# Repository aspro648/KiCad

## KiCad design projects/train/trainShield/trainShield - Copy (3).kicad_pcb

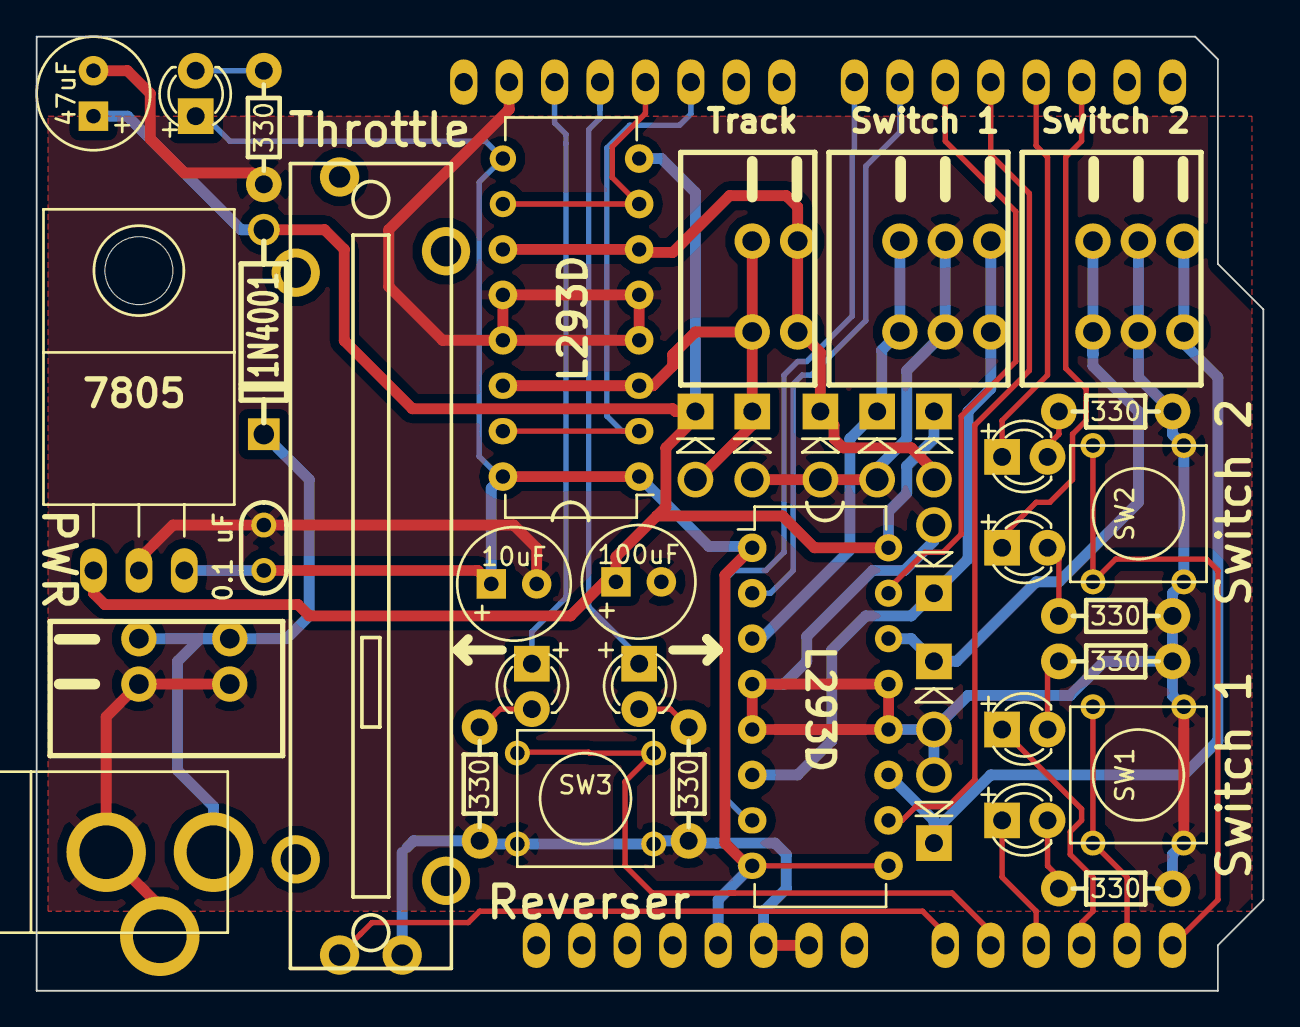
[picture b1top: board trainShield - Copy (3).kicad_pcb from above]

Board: 2 copper layers, 68.6 x 53.3 mm, 42 parts (0 on the bottom side), 33 nets.

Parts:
C1: 0.1 uF; C1
C2: 47uF; C2
C3: 100uF; C2
C4: 10uF; C2
C7: CTRIM; BOURNS-PTA3043_30mm-slide-pot
CON1: BARREL_JACK
D1: 1N4001
D2, D3, D4, D5, D6, D7, D8, D9: 1N4001; Diode_DO-41_SOD81_Vertical_AnodeUp
D10, D11, D12, D13, D14, D15, D16: LED; LED-3MM
P1, P3: TERM_2; TERMx2
P2, P4: TERMx3
R1, R2, R3, R4, R5, R6, R7: 330; Resistor_Horz
SHIELD1: ARDUINO_SHIELD
SW1, SW2, SW3: SW_PUSHBUTTON; SW_PUSH_SMALL
U1: 7805; TO-220_Neutral123_Horizontal
U2, U3: L293D; DIP-16_W7.62mm
VAL: MadeInOregonRev25
VAL#2: MB225rev

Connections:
+5V: C1.1, C4.1, D12.2, SHIELD1.5V, U1.VO, U2.1, U2.9, U2.16, U3.1, U3.8, U3.9
+12V: C2.1, C3.1, D1.1, D2.1, D7.1, U1.VI, U2.8, U3.16
/MOT_A: SHIELD1.11, U2.7, U2.10
/MOT_B: SHIELD1.10, U2.2, U2.15
/M_1: D3.1, D7.2, P1.1, U2.6, U2.11
/M_2: D2.2, D4.1, P1.2, U2.3, U2.14
/TURN_1_A: SHIELD1.5, U3.15
/TURN_1_B: SHIELD1.4, U3.10
/TURN_2_A: SHIELD1.6, U3.2
/TURN_2_B: SHIELD1.7, U3.7
GND: C1.2, C2.2, C3.2, C4.2, C7.2, CON1.2, CON1.3, D3.2, D4.2, D5.2, D6.2, D8.2, D9.2, P2.2, P3.2, P4.2, R1.1, R2.1, R3.1, R4.1, R5.1, R6.1, R7.1, SHIELD1.GND1, SHIELD1.GND2, SHIELD1.GND3, SW1.2, SW2.2, SW3.2, U1.GND, U2.4, U2.5, U2.12, U2.13, U3.4, U3.5, U3.12, U3.13
unnamed: C7.1, SHIELD1.AD0
unnamed: CON1.1, D1.2, P3.1
unnamed: D5.1, P2.3, U3.14
unnamed: D6.1, P2.1, U3.11
unnamed: D8.1, P4.3, U3.3
unnamed: D9.1, P4.1, U3.6
unnamed: D10.1, R5.2
unnamed: D10.2, SHIELD1.12
unnamed: D11.1, R6.2
unnamed: D11.2, SHIELD1.13
unnamed: D12.1, R1.2
unnamed: D13.1, R2.2
unnamed: D13.2, SHIELD1.3
unnamed: D14.1, R3.2
unnamed: D14.2, SHIELD1.2
unnamed: D15.1, R4.2
unnamed: D15.2, SHIELD1.AD3
unnamed: D16.1, R7.2
unnamed: D16.2, SHIELD1.AD2
unnamed: SHIELD1.AD1, SW3.1
unnamed: SHIELD1.AD4, SW1.1
unnamed: SHIELD1.AD5, SW2.1

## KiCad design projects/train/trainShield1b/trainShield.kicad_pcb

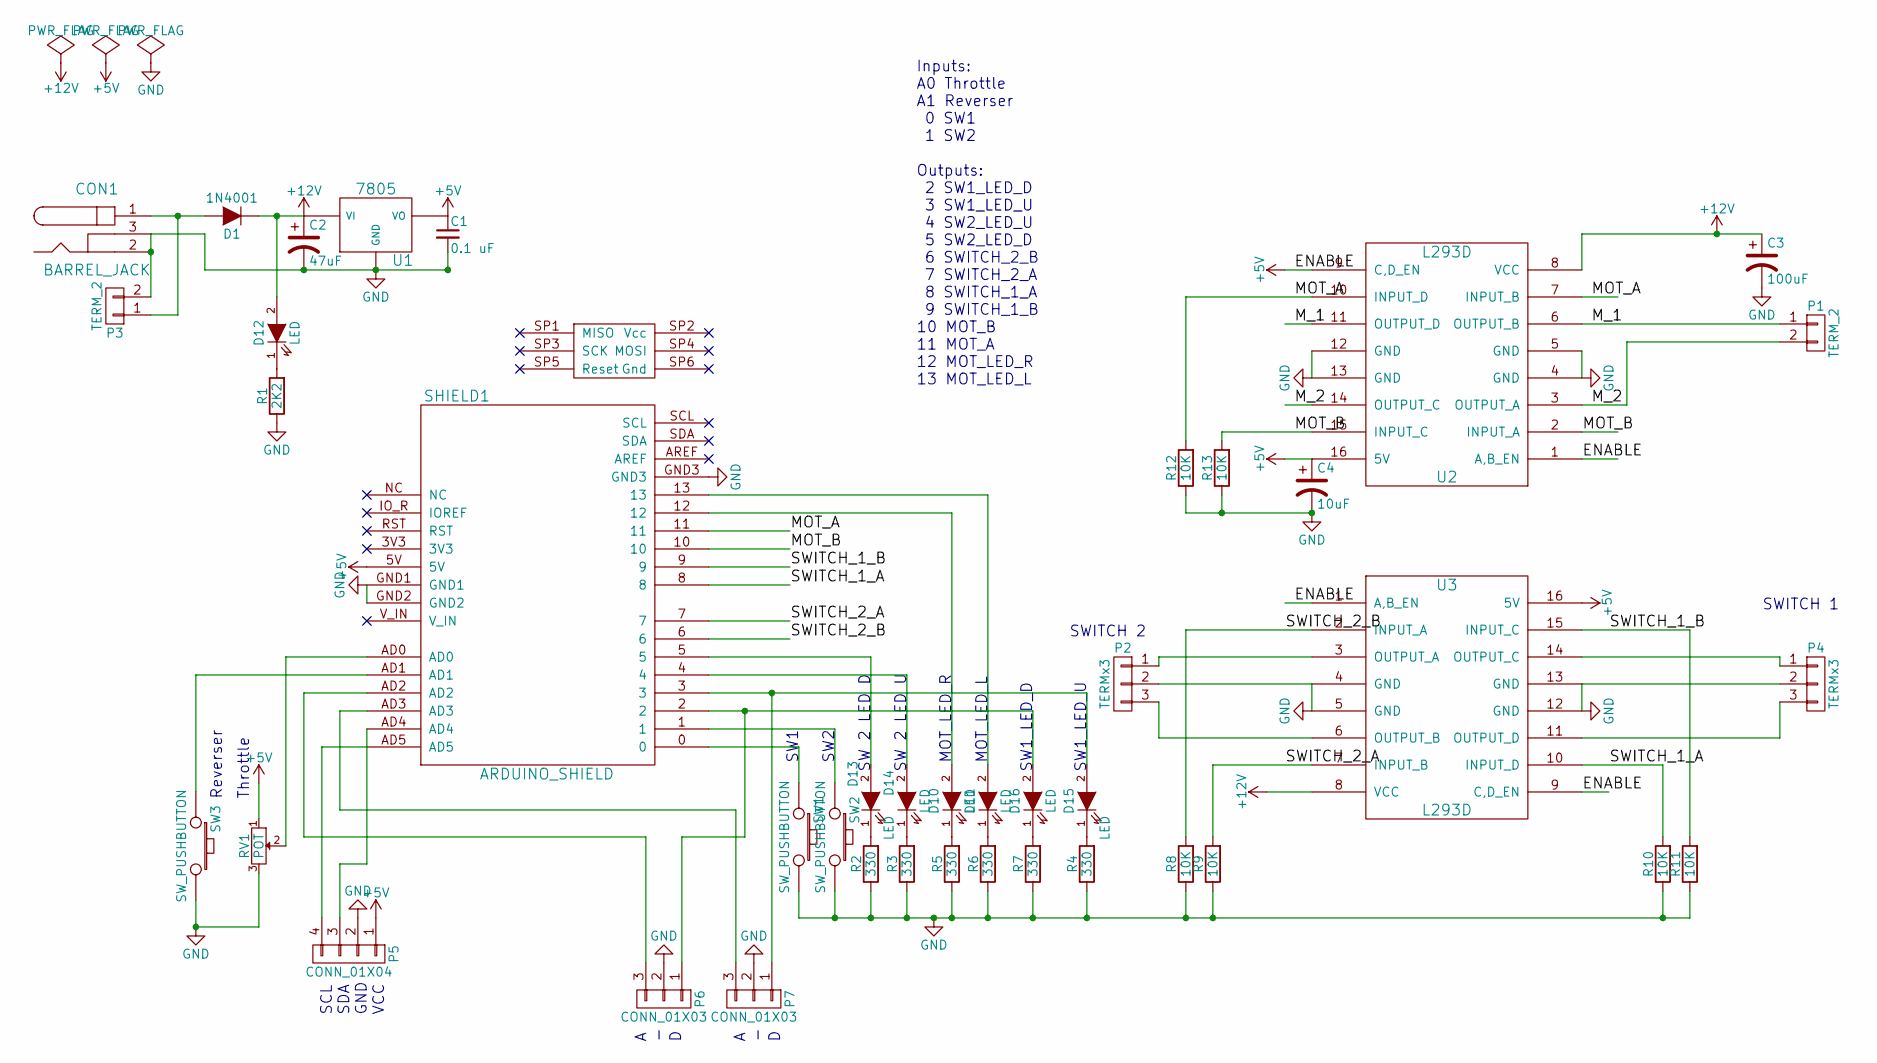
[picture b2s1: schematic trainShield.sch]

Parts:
C1: 0.1 uF; C1
C2: 47uF; C2
C3: 100uF; C2
C4: 10uF; C2
CON1: BARREL_JACK
D1: 1N4001
D10, D11, D12, D13, D14, D15, D16: LED; LED-3MM
P1, P3: TERM_2; TERMx2
P2, P4: TERMx3
P5: CONN_01X04; Pin_Header_Straight_1x04
P6, P7: CONN_01X03; TerminalBlock_Pheonix_MPT-2.54mm_3pol
R1: 2K2; Resistor_Horz
R2, R3, R4, R5, R6, R7: 330; Resistor_Horz
R8, R9, R10, R11, R12, R13: 10K; Resistor_Horz
RV1: POT
SHIELD1: ARDUINO_SHIELD
SW1, SW2, SW3: SW_PUSHBUTTON; SW_PUSH_SMALL
U1: 7805; TO-220_Neutral123_Horizontal
U2, U3: L293D; DIP-16_W7.62mm

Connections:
+5V: C1.1, C4.1, P5.1, RV1.1, SHIELD1.5V, U1.VO, U2.1 (A,B_EN), U2.9 (C,D_EN), U2.16 (5V), U3.1 (A,B_EN), U3.9 (C,D_EN), U3.16 (5V)
+12V: C2.1, C3.1, D1.1 (K), D12.2 (A), U1.VI, U2.8 (VCC), U3.8 (VCC)
/MOT_A: R12.2, SHIELD1.11, U2.7 (INPUT_B), U2.10 (INPUT_D)
/MOT_B: R13.2, SHIELD1.10, U2.2 (INPUT_A), U2.15 (INPUT_C)
/M_1: P1.1, U2.6 (OUTPUT_B), U2.11 (OUTPUT_D)
/M_2: P1.2, U2.3 (OUTPUT_A), U2.14 (OUTPUT_C)
/SWITCH_1_A: R10.2, SHIELD1.8, U3.10 (INPUT_D)
/SWITCH_1_B: R11.2, SHIELD1.9, U3.15 (INPUT_C)
/SWITCH_2_A: R9.2, SHIELD1.7, U3.7 (INPUT_B)
/SWITCH_2_B: R8.2, SHIELD1.6, U3.2 (INPUT_A)
GND: C1.2, C2.2, C3.2, C4.2, CON1.2, CON1.3, P2.2, P3.2, P4.2, P5.2, P6.2, P7.2, R1.1, R2.1, R3.1, R4.1, R5.1, R6.1, R7.1, R8.1, R9.1, R10.1, R11.1, R12.1, R13.1, RV1.3, SHIELD1.GND1, SHIELD1.GND2, SHIELD1.GND3, SW1.2, SW2.2, SW3.2, U1.GND, U2.4 (GND), U2.5 (GND), U2.12 (GND), U2.13 (GND), U3.4 (GND), U3.5 (GND), U3.12 (GND), U3.13 (GND)
unnamed: CON1.1, D1.2 (A), P3.1
unnamed: D10.1 (K), R5.2
unnamed: D10.2 (A), SHIELD1.12
unnamed: D11.1 (K), R6.2
unnamed: D11.2 (A), SHIELD1.13
unnamed: D12.1 (K), R1.2
unnamed: D13.1 (K), R2.2
unnamed: D13.2 (A), SHIELD1.5
unnamed: D14.1 (K), R3.2
unnamed: D14.2 (A), SHIELD1.4
unnamed: D15.1 (K), R4.2
unnamed: D15.2 (A), P7.1, SHIELD1.3
unnamed: D16.1 (K), R7.2
unnamed: D16.2 (A), P6.1, SHIELD1.2
unnamed: P2.1, U3.3 (OUTPUT_A)
unnamed: P2.3, U3.6 (OUTPUT_B)
unnamed: P4.1, U3.14 (OUTPUT_C)
unnamed: P4.3, U3.11 (OUTPUT_D)
unnamed: P5.3, SHIELD1.AD4
unnamed: P5.4, SHIELD1.AD5
unnamed: P6.3, SHIELD1.AD2
unnamed: P7.3, SHIELD1.AD3
unnamed: RV1.2, SHIELD1.AD0
unnamed: SHIELD1.0, SW1.1
unnamed: SHIELD1.1, SW2.1
unnamed: SHIELD1.AD1, SW3.1

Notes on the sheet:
Reverser
Throttle
SW1_LED_U
SW1_LED_D
SW1
SW2
MOT_LED_L
MOT_LED_R
SW 2 LED U
SW 2 LED D
Inputs: A0 Throttle A1 Reverser 0 SW1 1 SW2 Outputs: 2 SW1_LED_D 3 SW1_LED_U 4 SW2_LED_U 5 SW2_LED_D 6 SWITCH_2_B 7 SWITCH_2_A 8 SWITCH_1_A 9 SWITCH_1_B 10 MOT_B 11 MOT_A 12 MOT_LED_R 13 MOT_LED_L
SCL SDA GND VCC
A - D
SWITCH 2
SWITCH 1

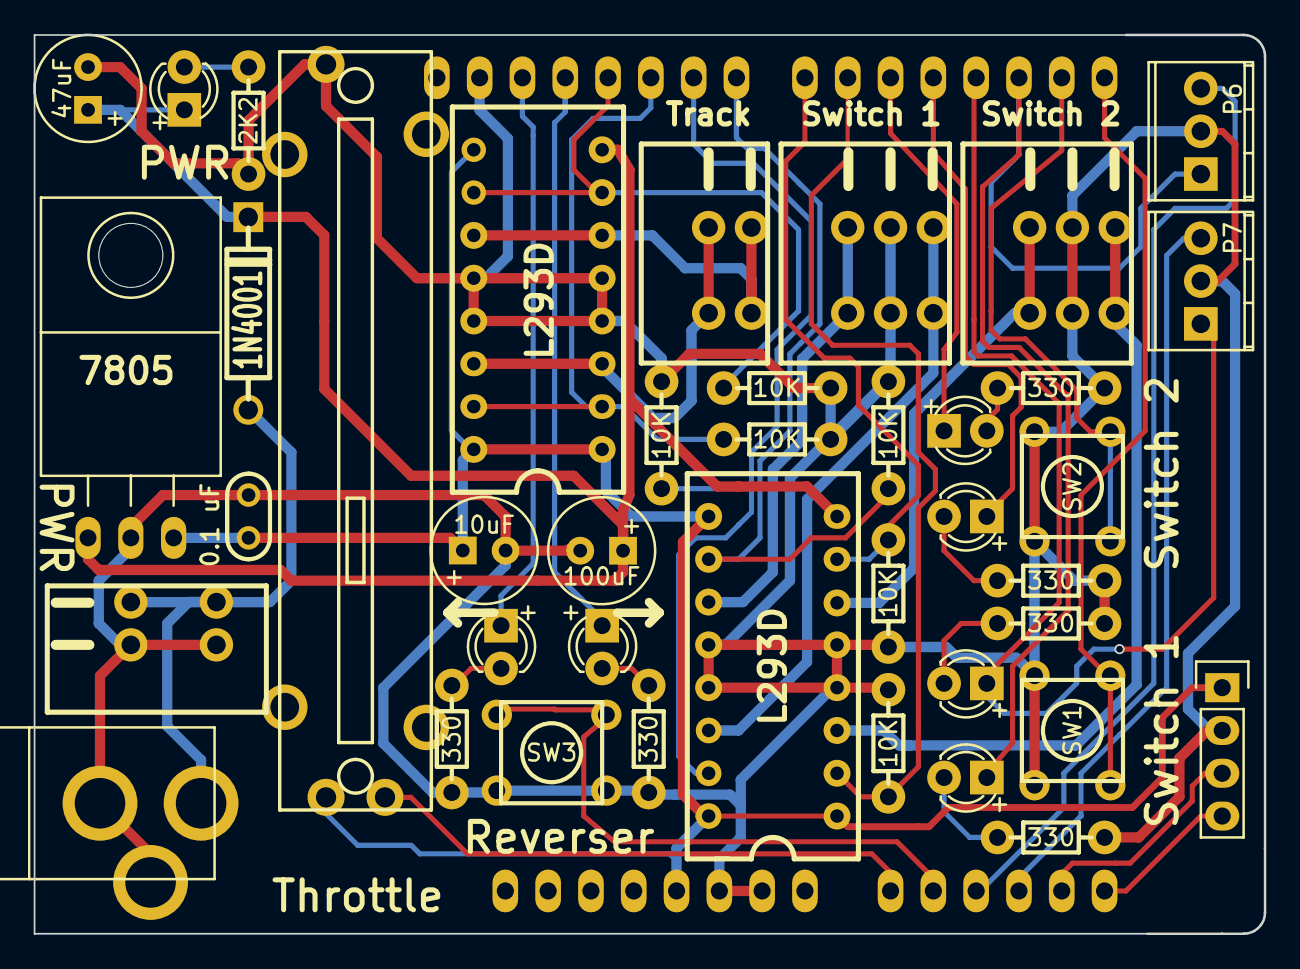
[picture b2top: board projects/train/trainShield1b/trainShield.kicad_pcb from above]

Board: 2 copper layers, 73.0 x 53.3 mm, 44 parts (0 on the bottom side), 37 nets.

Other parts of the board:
1X01: val**; 1X01
VAL: MadeInOregonRev25
VAL#2: MB225rev

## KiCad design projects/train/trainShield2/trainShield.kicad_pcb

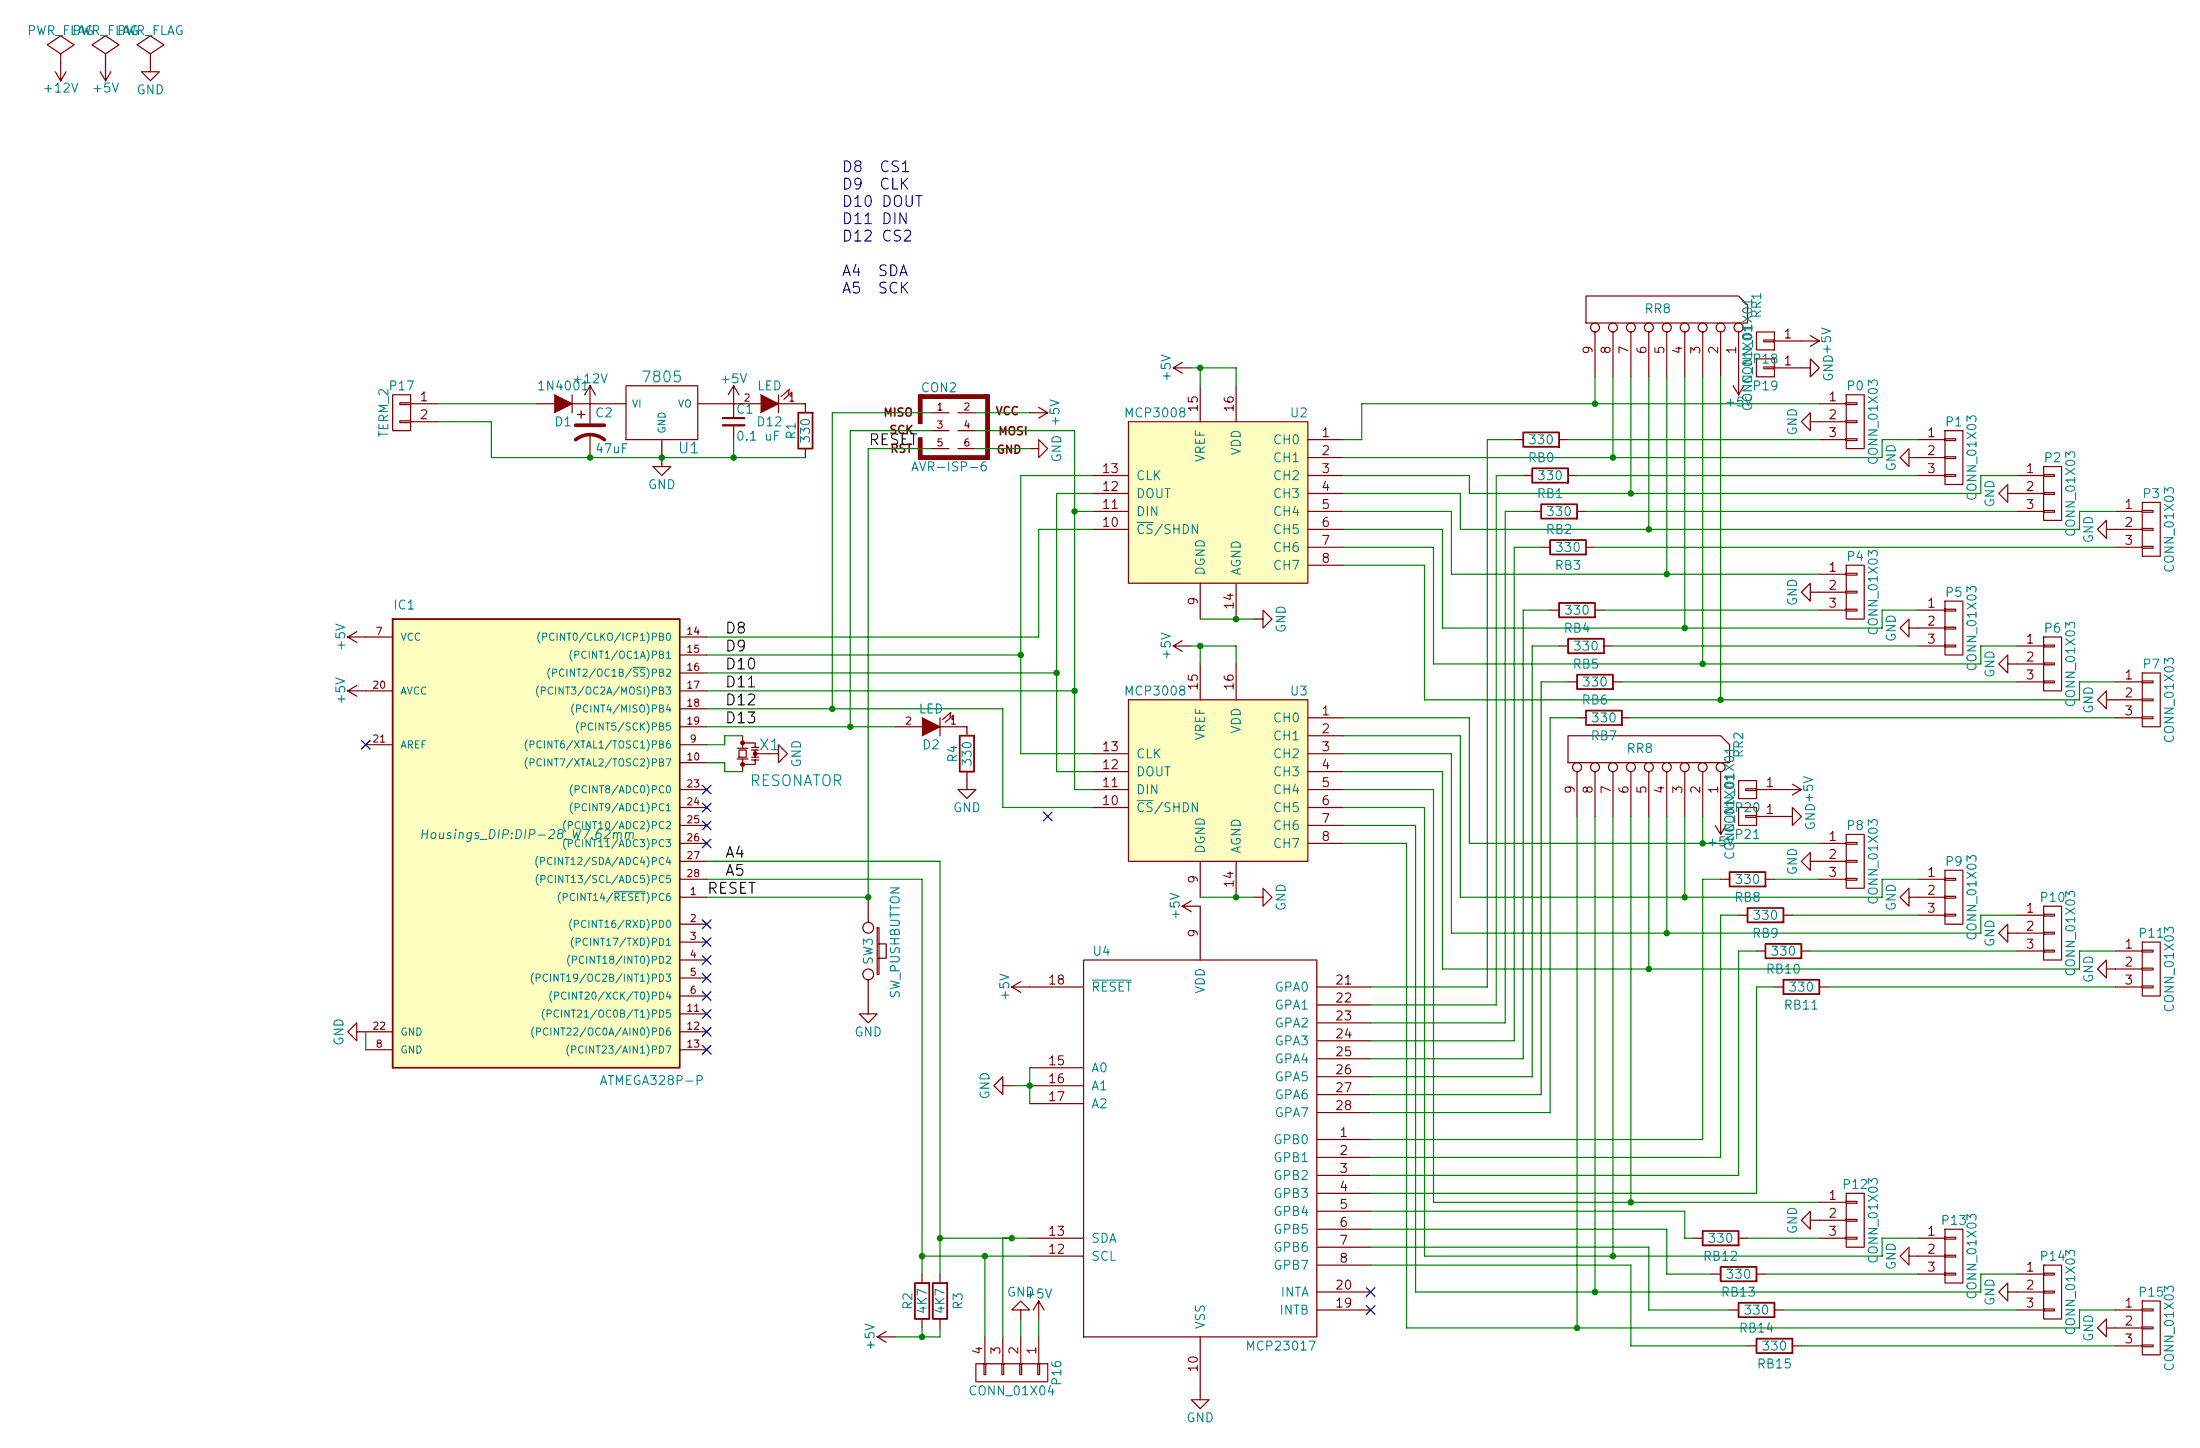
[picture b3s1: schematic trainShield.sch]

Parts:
C1: 0.1 uF; C1
C2: 47uF; C2
CON2: AVR-ISP-6
D1: 1N4001
D2, D12: LED; LED-3MM
IC1: ATMEGA328P-P; DIP-28_W7.62mm
P0, P1, P2, P3, P4, P5, P6, P7, P8, P9, P10, P11, P12, P13, P14, P15: CONN_01X03; TerminalBlock_Pheonix_MPT-2.54mm_3pol
P16: CONN_01X04; Pin_Header_Straight_1x04
P17: TERM_2; TerminalBlock_Pheonix_PT-3.5mm_2pol
P18, P19, P20, P21: CONN_01X01; Pin_Header_Straight_1x01
R1, R4: 330; Resistor_Horz
R2, R3: 4K7; Resistor_Horz
RB0, RB1, RB2, RB3, RB4, RB5, RB6, RB7, RB8, RB9, RB10, RB11, RB12, RB13, RB14, RB15: 330; Resistor_Horz
RR1, RR2: RR8; Resistor_Array_SIP8
SW3: SW_PUSHBUTTON; SW_PUSH_SMALL
U1: 7805; TO-220_Neutral123_Horizontal
U2, U3: MCP3008; DIP-16_W7.62mm
U4: MCP23017; DIP-28_W7.62mm
X1: RESONATOR; resonator_sip3

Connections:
+5V: C1.1, CON2.2, D12.2 (A), IC1.7 (VCC), IC1.20 (AVCC), P16.1, P18.1, P20.1, R2.1, R3.1, RR1.1 (COM), RR2.1 (COM), U1.VO, U2.15 (VREF), U2.16 (VDD), U3.15 (VREF), U3.16 (VDD), U4.9 (VDD), U4.18 (~RESET)
+12V: C2.1, D1.1 (K), U1.VI
/A4: IC1.27 ((PCINT12/SDA/ADC4)PC4), P16.3, R3.2, U4.13 (SDA)
/A5: IC1.28 ((PCINT13/SCL/ADC5)PC5), P16.4, R2.2, U4.12 (SCL)
/D8: IC1.14 ((PCINT0/CLKO/ICP1)PB0), U2.10 (~CS~/SHDN)
/D9: IC1.15 ((PCINT1/OC1A)PB1), U2.13 (CLK), U3.13 (CLK)
/D10: IC1.16 ((PCINT2/OC1B/~SS~)PB2), U2.12 (DOUT), U3.12 (DOUT)
/D11: CON2.4, IC1.17 ((PCINT3/OC2A/MOSI)PB3), U2.11 (DIN), U3.11 (DIN)
/D12: CON2.1, IC1.18 ((PCINT4/MISO)PB4), U3.10 (~CS~/SHDN)
/D13: CON2.3, D2.2 (A), IC1.19 ((PCINT5/SCK)PB5)
/RESET: CON2.5, IC1.1 ((PCINT14/~RESET~)PC6), SW3.1
GND: C1.2, C2.2, CON2.6, IC1.8 (GND), IC1.22 (GND), P0.2, P1.2, P2.2, P3.2, P4.2, P5.2, P6.2, P7.2, P8.2, P9.2, P10.2, P11.2, P12.2, P13.2, P14.2, P15.2, P16.2, P17.2, P19.1, P21.1, R1.1, R4.1, SW3.2, U1.GND, U2.9 (DGND), U2.14 (AGND), U3.9 (DGND), U3.14 (AGND), U4.10 (VSS), U4.15 (A0), U4.16 (A1), U4.17 (A2), X1.2
unnamed: D1.2 (A), P17.1
unnamed: D2.1 (K), R4.2
unnamed: D12.1 (K), R1.2
unnamed: IC1.9 ((PCINT6/XTAL1/TOSC1)PB6), X1.3
unnamed: IC1.10 ((PCINT7/XTAL2/TOSC2)PB7), X1.1
unnamed: P0.1, RR1.9, U2.1 (CH0)
unnamed: P0.3, RB0.2
unnamed: P1.1, RR1.8, U2.2 (CH1)
unnamed: P1.3, RB1.2
unnamed: P2.1, RR1.7, U2.3 (CH2)
unnamed: P2.3, RB2.2
unnamed: P3.1, RR1.6, U2.4 (CH3)
unnamed: P3.3, RB3.2
unnamed: P4.1, RR1.5, U2.5 (CH4)
unnamed: P4.3, RB4.2
unnamed: P5.1, RR1.4, U2.6 (CH5)
unnamed: P5.3, RB5.2
unnamed: P6.1, RR1.3, U2.7 (CH6)
unnamed: P6.3, RB6.2
unnamed: P7.1, RR1.2, U2.8 (CH7)
unnamed: P7.3, RB7.2
unnamed: P8.1, RR2.2, U3.1 (CH0)
unnamed: P8.3, RB8.2
unnamed: P9.1, RR2.3, U3.2 (CH1)
unnamed: P9.3, RB9.2
unnamed: P10.1, RR2.4, U3.3 (CH2)
unnamed: P10.3, RB10.2
unnamed: P11.1, RR2.5, U3.4 (CH3)
unnamed: P11.3, RB11.2
unnamed: P12.1, RR2.6, U3.5 (CH4)
unnamed: P12.3, RB12.2
unnamed: P13.1, RR2.7, U3.6 (CH5)
unnamed: P13.3, RB13.2
unnamed: P14.1, RR2.8, U3.7 (CH6)
unnamed: P14.3, RB14.2
unnamed: P15.1, RR2.9, U3.8 (CH7)
unnamed: P15.3, RB15.2
unnamed: RB0.1, U4.21 (GPA0)
unnamed: RB1.1, U4.22 (GPA1)
unnamed: RB2.1, U4.23 (GPA2)
unnamed: RB3.1, U4.24 (GPA3)
unnamed: RB4.1, U4.25 (GPA4)
unnamed: RB5.1, U4.26 (GPA5)
unnamed: RB6.1, U4.27 (GPA6)
unnamed: RB7.1, U4.28 (GPA7)
unnamed: RB8.1, U4.1 (GPB0)
unnamed: RB9.1, U4.2 (GPB1)
unnamed: RB10.1, U4.3 (GPB2)
unnamed: RB11.1, U4.4 (GPB3)
unnamed: RB12.1, U4.5 (GPB4)
unnamed: RB13.1, U4.6 (GPB5)
unnamed: RB14.1, U4.7 (GPB6)
unnamed: RB15.1, U4.8 (GPB7)

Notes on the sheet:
D8 CS1 D9 CLK D10 DOUT D11 DIN D12 CS2 A4 SDA A5 SCK

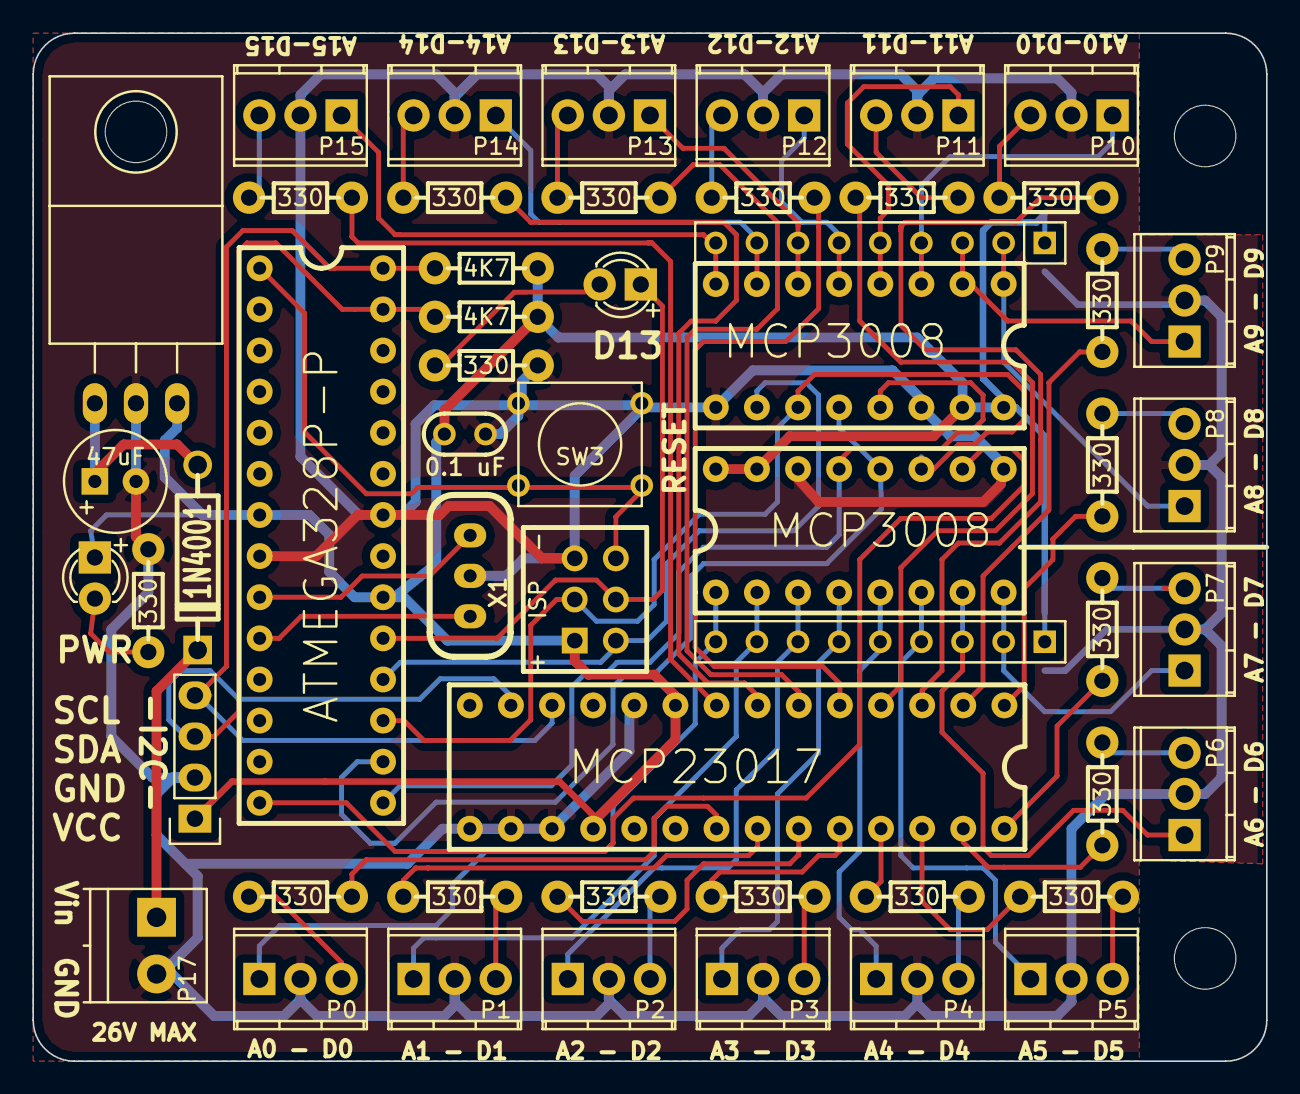
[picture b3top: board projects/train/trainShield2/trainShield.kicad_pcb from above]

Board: 2 copper layers, 76.2 x 63.5 mm, 59 parts (0 on the bottom side), 65 nets.

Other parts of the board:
VAL: MB225rev
VAL#2: MadeInOregonRev25

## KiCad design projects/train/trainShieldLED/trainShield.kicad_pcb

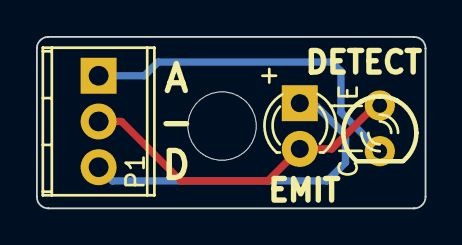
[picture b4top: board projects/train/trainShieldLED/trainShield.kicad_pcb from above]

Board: 2 copper layers, 21.6 x 9.5 mm, 3 parts (0 on the bottom side), 3 nets.

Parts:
D1: LED; LED-3MM
P1: CONN_01X03; TerminalBlock_Pheonix_MPT-2.54mm_3pol
Q1: OPTO_NPN; PHOTO_TRANS

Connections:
unnamed: D1.1, P1.2, Q1.1
unnamed: D1.2, P1.3
unnamed: P1.1, Q1.3

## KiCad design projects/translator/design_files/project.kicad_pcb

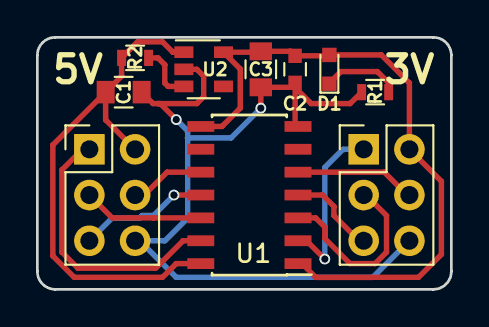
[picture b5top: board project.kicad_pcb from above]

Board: 2 copper layers, 23.0 x 14.0 mm, 10 parts (0 on the bottom side), 13 nets.

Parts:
C1, C3: 10uF; C_0805
C2: 1uF; C_0603
CON1, CON2: AVR-ISP-6; Pin_Header_Straight_2x03_Pitch2.54mm
D1: LED; LED_0603
R1: 330; R_0603
R2: 100K; R_0603
U1: TXB0104D; SOIC-14_3.9x8.7mm_Pitch1.27mm
U2: MIC5225-3.3; SOT-23-5

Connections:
+3V3: C2.1, C3.1, CON2.2, D1.2, U1.1, U1.8, U2.5
+5V: C1.1, CON1.2, R2.2, U1.14, U2.1
/MISO_3V: CON2.1, U1.2
/MISO_5V: CON1.1, U1.13
/MOSI_3V: CON2.4, U1.5
/MOSI_5V: CON1.4, U1.10
/SCK_3V: CON2.3, U1.3
/SCK_5V: CON1.3, U1.12
/~RESET_3V: CON2.5, U1.4
/~RESET_5V: CON1.5, U1.11
GND: C1.2, C2.2, C3.2, CON1.6, CON2.6, R1.2, U1.7, U2.2
unnamed: D1.1, R1.1
unnamed: R2.1, U2.3
